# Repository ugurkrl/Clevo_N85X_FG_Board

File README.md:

# Clevo_N85X_FG_Board
Archived because i no longer have any Clevo laptop.
But this design works fine. Just tie FUSE pin to ground. Also dont forget to switch order of SDA and SCL pins !
I used this design longer than 2 years and i had no stability issues. Just make sure your BQ40z50 or 4050 settings are OK

BQ40z50/BQ4050 Fuel Gauge board for Clevo N850/5/7(Monster A5 V9) notebook computers.

**Issues**
1. Fix reverted SDA SCL 
1. bypass fuse pin

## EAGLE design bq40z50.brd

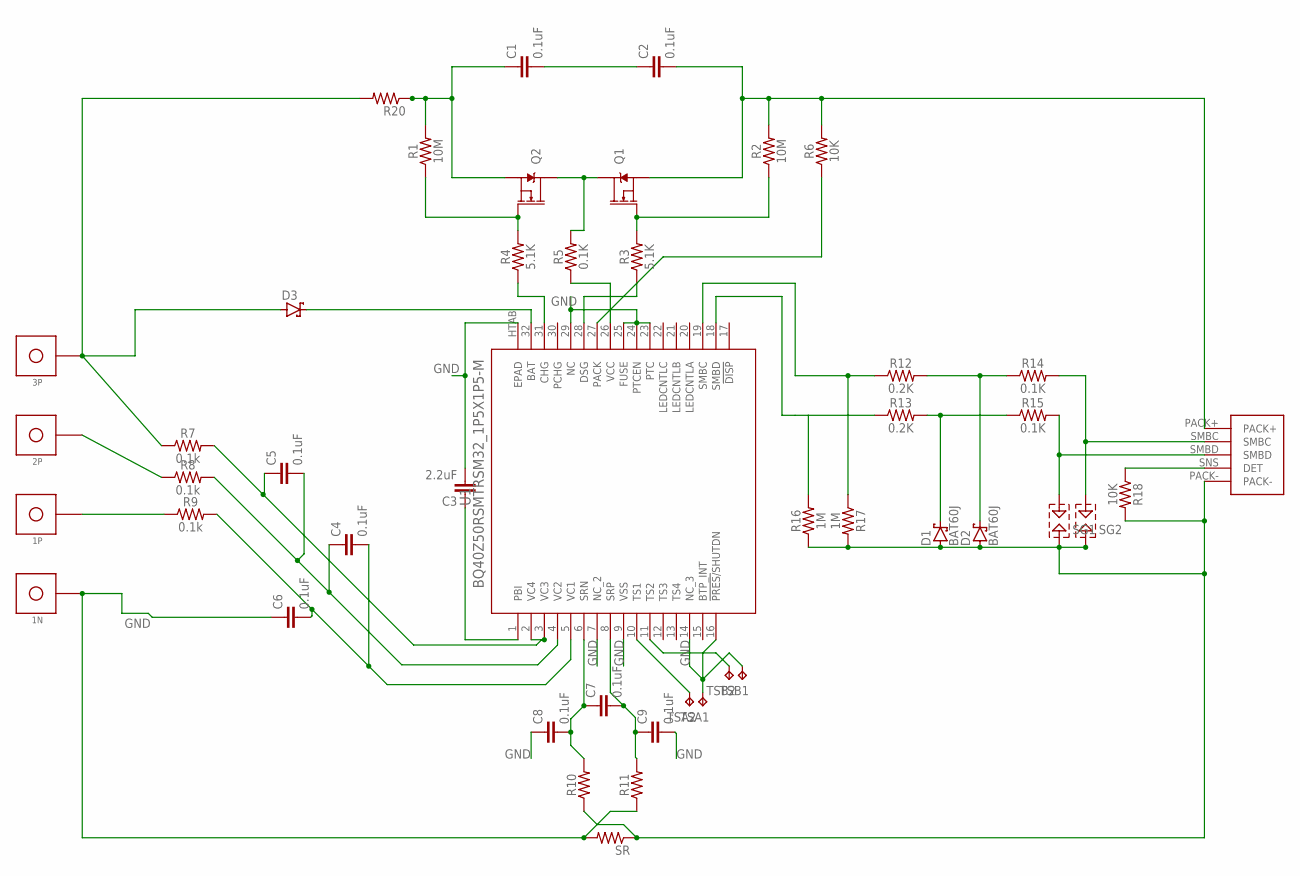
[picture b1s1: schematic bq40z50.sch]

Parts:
1N, 1P, 2P, 3P: BAT_TAB; BATT_TAB
C1, C2, C4, C5, C6, C7, C8, C9: 0.1uF; 0402
C3: 2.2uF; 0402
D1, D2, D3: BAT60J; SOD323_ST
Q1, Q2: 6.5A/30V/38mΩ; SO08
R1, R2: 10M; 0402
R3, R4: 5.1K; 0402
R5, R14, R15: 0.1K; 0402
R6, R18: 10K; 0402
R7, R8, R9: 0.1k; 0402
R10, R11: 0402
R12, R13: 0.2K; 0402
R16, R17: 1M; 0402
R20: R-US_R2512; R2512
SG1, SG2: SPARK-GAP-8
SR: R-US_R2512; R2512
TSA1, TSA2: TPTP18R; TP18R
TSB1, TSB2: TPTP18R; TP18R
U1: BQ40Z50RSMTRSM32_1P5X1P5-M; RSM32_1P5X1P5-M
U$1: N857HK1_FG; N850BAT

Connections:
GND: 1N.P$1, C3.2, C6.1, C8.1, C9.2, R11.1, SR.2, TSA1.TP, TSB1.TP, U1.7 (NC_2), U1.9 (VSS), U1.14 (NC_3), U1.16 (!PRES/!SHUTDN), U1.23 (PTC), U1.24 (PTCEN), U1.25 (FUSE), U1.29 (NC), U1.HTAB (EPAD)
unnamed: Q2.4 (G), R1.1, R4.2
unnamed: 3P.P$1, D3.A, R7.1, R20.2
unnamed: D1.A, D2.A, R10.1, R16.1, R17.2, R18.2, SG1.2, SG2.2, SR.1, U$1.PACK-
unnamed: C1.1, Q2.1 (S), Q2.2 (S), Q2.3 (S), R1.2, R20.1
unnamed: C1.2, C2.1
unnamed: C2.2, Q1.1 (S), Q1.2 (S), Q1.3 (S), R2.2, R6.2, U$1.PACK+
unnamed: Q1.5 (D), Q1.6 (D), Q1.7 (D), Q1.8 (D), Q2.5 (D), Q2.6 (D), Q2.7 (D), Q2.8 (D), R5.2
unnamed: Q1.4 (G), R2.1, R3.2
unnamed: R4.1, U1.31 (CHG)
unnamed: R3.1, U1.28 (DSG)
unnamed: R5.1, U1.26 (VCC)
unnamed: R6.1, U1.27 (PACK)
unnamed: D3.C, U1.32 (BAT)
unnamed: C3.1, U1.1 (PBI)
unnamed: C5.1, R7.2, U1.2 (VC4), U1.3 (VC3)
unnamed: 2P.P$1, R8.1
unnamed: 1P.P$1, R9.1
unnamed: C7.2, C9.1, R11.2, U1.8 (SRP)
unnamed: C4.1, C5.2, R8.2, U1.4 (VC2)
unnamed: C4.2, C6.2, R9.2, U1.5 (VC1)
unnamed: C7.1, C8.2, R10.2, U1.6 (SRN)
unnamed: TSA2.TP, U1.10 (TS1)
unnamed: TSB2.TP, U1.11 (TS2)
unnamed: R13.1, R16.2, U1.18 (SMBD)
unnamed: R12.1, R17.1, U1.19 (SMBC)
unnamed: D1.C, R13.2, R15.1
unnamed: D2.C, R12.2, R14.1
unnamed: R15.2, SG1.1, U$1.SMBD
unnamed: R14.2, SG2.1, U$1.SMBC
unnamed: R18.1, U$1.SNS (DET)

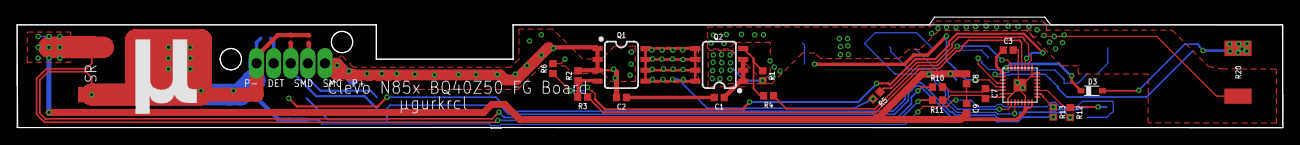
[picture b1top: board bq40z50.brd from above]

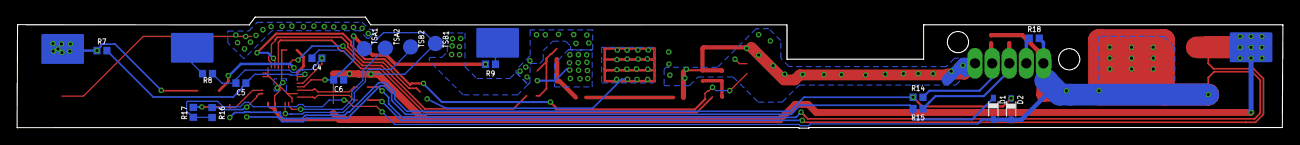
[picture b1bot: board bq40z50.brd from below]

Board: 2 copper layers, 148.0 x 13.0 mm, 46 parts (21 on the bottom side), 31 nets.

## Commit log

2019-08-14 schematic : fix reversed SMBC SMBD lines
2019-08-14 schematic : connect FUSE to GND (otherwise 40z50 doesn't enables FETs)
2019-08-14 schematic : spark gap mod
2019-08-14 board : apply schematic changes
2019-08-14 clean gerber files

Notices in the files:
parts and their libraries:
SparkFun-Resistors: Licensing: Creative Commons ShareAlike 4.0 International - https://creativecommons.org/licenses/by-sa/4.0
supressor: Copyright (C) 2009, Bob Starr
